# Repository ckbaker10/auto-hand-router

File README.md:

# Auto-Hand-Router

Curved tracks and teardrops for two-layer KiCad 10 boards.

Freerouting or J-Kreisel handles the connections. Auto-Hand-Router spreads and
smooths the tracks, adds teardrops and checks the result.

## Demos

### 555 timer

Eight nets, 291 native arcs and ten vias. Uses the built-in reference router.

[KiCad project](examples/555-reference/routed.kicad_pro) ·
[Board source and license](examples/555-reference/SOURCE-LICENSE.txt)

### Drying Oven Compact

70 × 90 mm, 2,287 arcs, 43 vias and 229 teardrop shoulders.
No ERC, DRC or schematic parity findings.

[KiCad project](examples/drying-oven-compact/drying-oven-compact.kicad_pro) ·
[Results](examples/drying-oven-compact/summary.json)

### Drying Fridge

120 × 100 mm, 2,568 arcs, 45 vias and 274 teardrop shoulders.
All connections closed. Existing library and metadata warnings are listed in the results.

[KiCad project](examples/drying-fridge/drying-fridge.kicad_pro) ·
[Results](examples/drying-fridge/summary.json)

### Pad and via transitions

Teardrops follow straight tracks and native arcs, including offset entries and
short connected pieces. Default size: 0.875.

## Setup

Linux, Python 3.12+, [uv](https://docs.astral.sh/uv/) and KiCad 10 with its
`pcbnew` Python module. Components must be on the front side.

```sh
git clone https://github.com/ckbaker10/auto-hand-router.git
cd auto-hand-router
uv sync --locked

kicad-cli version
/usr/bin/python3 -c 'import pcbnew; print(pcbnew.Version())'
```

If KiCad uses a different interpreter or is outside your PATH:

```sh
export AUTO_HAND_ROUTER_KICAD_CLI=/path/to/kicad-cli
export AUTO_HAND_ROUTER_KICAD_PYTHON=/path/to/python3
```

For the `route` command, choose one backend.

### Freerouting

Requires Java 25. Download the pinned 2.5.0 JAR:

```sh
mkdir -p "$HOME/.local/share/auto-hand-router"
curl -fL https://github.com/freerouting/freerouting/releases/download/v2.5.0/freerouting-2.5.0.jar \
  -o "$HOME/.local/share/auto-hand-router/freerouting-2.5.0.jar"

export AUTO_HAND_ROUTER_FREEROUTING_JAR="$HOME/.local/share/auto-hand-router/freerouting-2.5.0.jar"
```

The router checks the JAR checksum.

### J-Kreisel

```sh
uv sync --locked --extra kreisel
```

A Rust toolchain may be needed to build it. Use
`uv run --locked --extra kreisel auto-hand-router route --backend kreisel`
with the board, output and work options below.

## Route a board

Keep the PCB, project and schematic together with the same filename stem:
`controller.kicad_pcb`, `controller.kicad_pro`, `controller.kicad_sch`.
Existing project rules and library tables are used.

```sh
uv run --locked auto-hand-router route \
  --board /path/to/controller.kicad_pcb \
  --output-dir output/controller \
  --work-dir work/controller-001 \
  --spacing 1.2 \
  --teardrop-size 0.875
```

This uses Freerouting. The source project stays unchanged.
The output contains the KiCad project, SVG/PNG previews and `report.json`.
Use a new work directory for each run.

| Option | Effect |
| --- | --- |
| `--spacing 1.2` | Preferred extra clearance in mm. Minimum project clearances still apply. |
| `--via-policy courtyards` | Default. Keeps vias outside component courtyards. |
| `--via-policy module-interiors` | Allows vias under large through-hole modules. Pad, drill and keepout clearances still apply. |
| `--radius 2.5` | Maximum radius for local fallback fillets, in mm. |
| `--teardrop-size 0.875` | Scales teardrop length and shoulders. |
| `--no-teardrops` | Disables teardrops. |

Project netclasses are used by default. Add
`--profile profiles/jlcpcb-2layer-1oz.json` to apply the included profile.
For this profile, put your power nets in `kicad-workflow.json` next to the board:

```json
{"routing": {"power_net_patterns": ["/+5V", "/+3V3", "/GND"]}}
```

## Add teardrops to an existing board

```sh
uv run --locked auto-hand-router teardrops \
  --board /path/to/controller.kicad_pcb \
  --output-dir output/controller-teardrops \
  --work-dir work/controller-teardrops-001 \
  --size 0.875
```

This keeps the existing tracks and adds copper zones at pads and vias.
Both directories must be new. Use `--length-ratio` and `--max-length` to
adjust the shape. Add `--via-policy module-interiors` if the board already
uses vias under modules.

## Reproduce the demos

The routed projects shown above are included in `examples/`.

Generate the 555 routing and then add teardrops. No external routing backend is needed:

```sh
uv run --locked auto-hand-router --comparison --output-dir output/555

uv run --locked auto-hand-router teardrops \
  --board output/555/routed.kicad_pcb \
  --output-dir output/555-teardrops \
  --work-dir work/555-teardrops-001
```

Rebuild teardrops and previews for the two larger demos:

```sh
uv run --locked auto-hand-router teardrops \
  --board examples/drying-oven-compact/drying-oven-compact.kicad_pcb \
  --output-dir output/oven-teardrops \
  --work-dir work/oven-teardrops-001 \
  --via-policy module-interiors

uv run --locked auto-hand-router teardrops \
  --board examples/drying-fridge/drying-fridge.kicad_pcb \
  --output-dir output/fridge-teardrops \
  --work-dir work/fridge-teardrops-001
```

To reroute either project, use its PCB with the `route` command.
The Compact uses J-Kreisel; the Fridge uses Freerouting.

Run the checks and build the package:

```sh
uv run --locked pytest -q
uv run --locked ruff check auto_hand_router comparison tests tools/sync_project_examples.py
uv build
```

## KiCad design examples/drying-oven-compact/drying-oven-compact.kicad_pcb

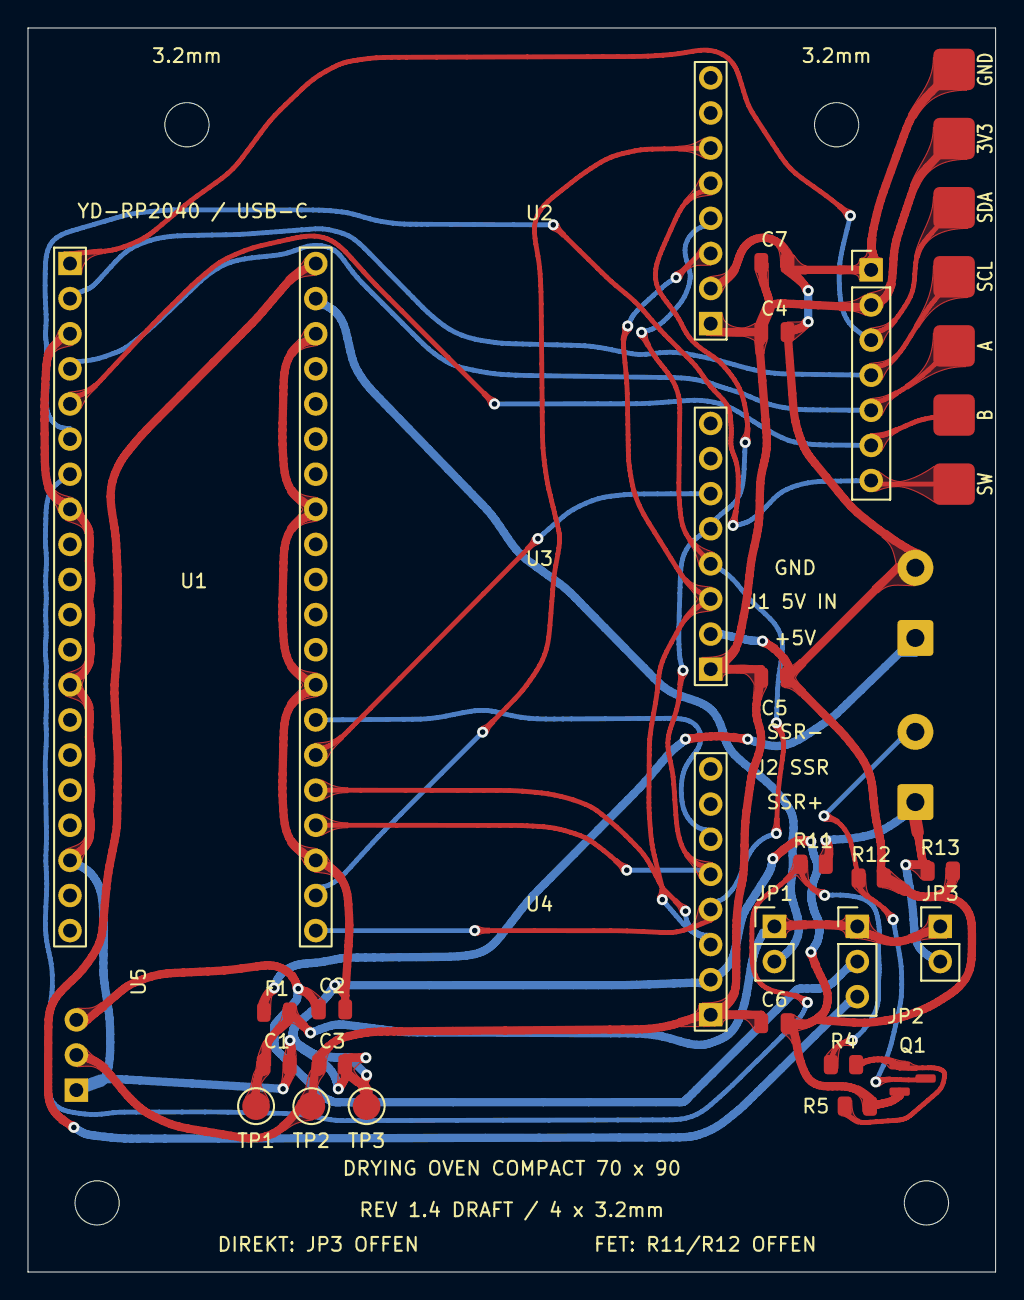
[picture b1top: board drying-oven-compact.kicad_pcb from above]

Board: 2 copper layers, 70.0 x 90.0 mm, 33 parts (0 on the bottom side), 22 nets.

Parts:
C1, C2, C3: 10u / 10V; JLC_C_0805_2012Metric
C4, C5, C6, C7: 100n / 10V; JLC_C_0805_2012Metric
F1: 0.5A HOLD / >=6V; JLC_Fuse_0805_2012Metric
H1, H2, H3, H4: M3; MountingHole_3.2mm_M3
J1: PS1 -> TRAEGER / 5V; TerminalBlock_1x02_P5.08_SilkClear
J2: SSR STEUERKABEL; TerminalBlock_1x02_P5.08_SilkClear
J3: DISPLAY-LOETPADS; Display_Wire_SolderPads_1x07
J4: STECKEROPTION VORDERSEITE / DNP; JLC_PinHeader_1x07_P2.54mm_Vertical
JP1: MCU VIN FREIGABE; JLC_PinHeader_1x02_P2.54mm_Vertical
JP2: REG: 1-2 PSU / 2-3 USB; JLC_PinHeader_1x03_P2.54mm_Vertical
JP3: 5V NUR FET / OFFEN BEI DIREKT; JLC_PinHeader_1x02_P2.54mm_Vertical
Q1: AO3400A; JLC_SOT-23
R4: 100R; JLC_R_0805_2012Metric
R5: 100k / AUS BEI RESET; JLC_R_0805_2012Metric
R11, R12: 0R / NUR DIREKT; JLC_R_0805_2012Metric
R13: 10k / OPTIONAL DNP; JLC_R_0805_2012Metric
TP1: +5V_MAIN; JLC_TestPoint_Pad_D2.0mm
TP2: +3V3_EXT; JLC_TestPoint_Pad_D2.0mm
TP3: GND; JLC_TestPoint_Pad_D2.0mm
U1: RP2040 USB-C / 16MiB; JLC_YD_RP2040_40Pin_Socket
U2: MAX31856 / T1; JLC_MAX31856_D25_W23_8Pin_Socket_DRAFT
U3: MAX31856 / T2; JLC_MAX31856_D25_W23_8Pin_Socket_DRAFT
U4: MAX31856 / T3; JLC_MAX31856_D25_W23_8Pin_Socket_DRAFT
U5: AMS1117 Modul / 3.3V; AMS1117_Module_3Pin_DRAFT

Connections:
/+3V3_EXT: C3.1, C4.1, C5.1, C6.1, C7.1, J3.2, J4.2, TP2.1, U2.1, U3.1, U4.1, U5.2
/+5V_MAIN: C1.1, F1.2, JP1.1, JP2.1, JP3.1, TP1.1
/ENC_A: J3.5, J4.5, U1.4
/ENC_B: J3.6, J4.6, U1.5
/ENC_SW: J3.7, J4.7, U1.6
/GND: C1.2, C2.2, C3.2, C4.2, C5.2, C6.2, C7.2, J1.2, J3.1, J4.1, Q1.2, R5.2, R12.2, R13.2, TP3.1, U1.3, U1.8, U1.13, U1.18, U1.23, U1.28, U1.33, U1.38, U2.2, U3.2, U4.2, U5.1
/I2C_SCL: J3.4, J4.4, U1.2
/I2C_SDA: J3.3, J4.3, U1.1
/MCU_VIN: JP1.2, U1.39
/MCU_VOUT: JP2.3, U1.40
/PSU_5V_RAW: F1.1, J1.1
/REG_5V_IN: C2.1, JP2.2, U5.3
/SPI_MISO: U1.21, U2.4, U3.4, U4.4
/SPI_MOSI: U1.25, U2.3, U3.3, U4.3
/SPI_SCK: U1.24, U2.5, U3.5, U4.5
/SSR_CMD: R4.1, R11.1, U1.7
/SSR_GATE: Q1.1, R4.2, R5.1
/SSR_NEG: J2.2, Q1.3, R12.1
/SSR_POS: J2.1, JP3.2, R11.2, R13.1
/TC_CS1: U1.22, U2.6
/TC_CS2: U1.26, U3.6
/TC_CS3: U1.27, U4.6

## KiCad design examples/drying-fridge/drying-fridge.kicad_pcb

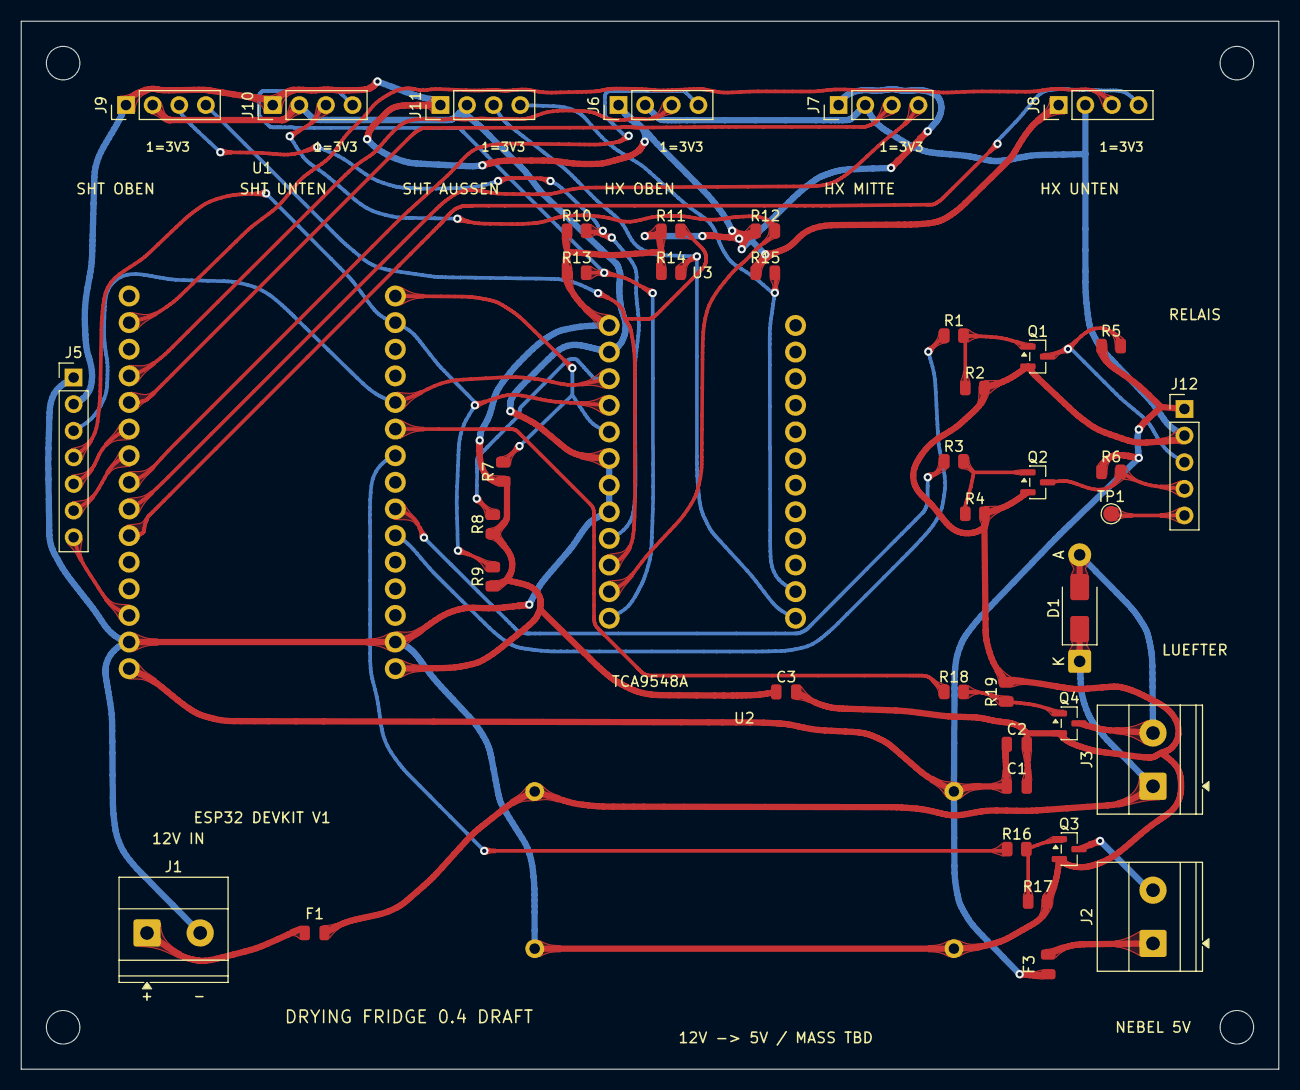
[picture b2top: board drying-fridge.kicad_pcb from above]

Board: 2 copper layers, 120.0 x 100.0 mm, 58 parts (0 on the bottom side), 37 nets.

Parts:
C1: 10u / >=10V; JLC_C_0805_2012Metric
C2, C3: 100n; JLC_C_0805_2012Metric
CT1: Kabelbinder J6; CableTie_2Slots_3.5x1.5_S8_DRAFT
CT2: Kabelbinder J7; CableTie_2Slots_3.5x1.5_S8_DRAFT
CT3: Kabelbinder J8; CableTie_2Slots_3.5x1.5_S8_DRAFT
CT4: Kabelbinder J9; CableTie_2Slots_3.5x1.5_S8_DRAFT
CT5: Kabelbinder J10; CableTie_2Slots_3.5x1.5_S8_DRAFT
CT6: Kabelbinder J11; CableTie_2Slots_3.5x1.5_S8_DRAFT
CT7: Kabelbinder J1; CableTie_2Slots_3.5x1.5_S8_DRAFT
CT8: Kabelbinder J2; CableTie_2Slots_3.5x1.5_S8_DRAFT
CT9: Kabelbinder J3; CableTie_2Slots_3.5x1.5_S8_DRAFT
CT10: Kabelbinder J12; CableTie_2Slots_3.5x1.5_S8_DRAFT
D1: Freilauf / Typ TBD; D_SMA_DO41_Combo_P10.16mm_D1.1
F1: AUX / Wert TBD; JLC_Fuse_0805_2012Metric
F3: NEBEL / Wert TBD; JLC_Fuse_0805_2012Metric
H1, H2, H3, H4: MountingHole_3.2mm_M3
J1: 12V IN / Versorgung; TerminalBlock_Phoenix_MKDS-1,5-2-5.08_1x02_P5.08mm_Horizont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
J2: NEBEL + / RETURN; TerminalBlock_Phoenix_MKDS-1,5-2-5.08_1x02_P5.08mm_Horizont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
J3: FAN power connector; TerminalBlock_Phoenix_MKDS-1,5-2-5.08_1x02_P5.08mm_Horizont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
J5: OLED / EC11 / 3V3 / OPTION; PinHeader_1x07_P2.54mm_Vertical
J6: HX711 OBEN; PinHeader_1x04_P2.54mm_Vertical
J7: HX711 MITTE; PinHeader_1x04_P2.54mm_Vertical
J8: HX711 UNTEN; PinHeader_1x04_P2.54mm_Vertical
J9: SHT40 OBEN; PinHeader_1x04_P2.54mm_Vertical
J10: SHT40 UNTEN; PinHeader_1x04_P2.54mm_Vertical
J11: SHT40 AUSSEN; PinHeader_1x04_P2.54mm_Vertical
J12: RELAIS STEUERUNG; PinHeader_1x05_P2.54mm_Vertical
Q1, Q2, Q3, Q4: AO3400A; SOT-23
R1, R3, R16, R18: 100; JLC_R_0805_2012Metric
R2, R4, R17, R19: 100k; JLC_R_0805_2012Metric
R5, R6, R7: 10k; JLC_R_0805_2012Metric
R8, R9, R10, R11, R12, R13, R14, R15: 4k7 DNP; JLC_R_0805_2012Metric
TP1: CTRL_COM / Modul pruefen; TestPoint_Pad_D1.5mm
U1: ESP32 DEVKIT V1 / ESP-WROOM-32 / 30pin; ESP32_DevKitV1_30Pin_D1.2_REF_DRAFT
U2: DC/DC 12V -> 5V / TBD; Fridge_DCDC_4Terminal_EST_DRAFT
U3: TCA9548A HW-617; TCA9548A_HW617_22x31_P17.78_D1.2_DRAFT

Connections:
/+3V3: C3.1, J5.2, J6.1, J7.1, J8.1, J9.1, J10.1, J11.1, R7.1, R8.1, R9.1, R10.1, R11.1, R12.1, R13.1, R14.1, R15.1, U1.R15 (3V3), U3.VIN
/+5V: C1.1, C2.1, F3.1, J12.1, R5.1, R6.1, U1.L15 (VIN), U2.OUT+
/+5V_MIST: F3.2, J2.1
/+12V_AUX: D1.1, F1.2, J3.1, U2.IN+
/+12V_IN: F1.1, J1.1
/ENC_A: J5.5, U1.L6 (D32_GPIO32)
/ENC_B: J5.6, U1.L7 (D33_GPIO33)
/ENC_SW: J5.7, U1.L13 (D13_GPIO13)
/FAN_EN: R18.1, U1.R6 (D19_GPIO19)
/FAN_GATE: Q4.1, R18.2, R19.1
/FAN_RETURN: D1.2, J3.2, Q4.3
/FRIDGE_EN: R3.1, U1.R9 (TX2_GPIO17)
/GND: C1.2, C2.2, C3.2, J1.2, J5.1, J6.2, J7.2, J8.2, J9.2, J10.2, J11.2, J12.2, Q1.2, Q2.2, Q3.2, Q4.2, R2.2, R4.2, R17.2, R19.2, U1.L14 (GND), U1.R14 (GND), U2.IN-, U2.OUT-, U3.A0, U3.A1, U3.A2, U3.GND
/HEAT_EN: R1.1, U1.R10 (RX2_GPIO16)
/HX_LOW_DT: J8.3, U1.L2 (VP_GPIO36)
/HX_LOW_SCK: J8.4, U1.L10 (D27_GPIO27)
/HX_MID_DT: J7.3, U1.L5 (D35_GPIO35)
/HX_MID_SCK: J7.4, U1.L9 (D26_GPIO26)
/HX_TOP_DT: J6.3, U1.L4 (D34_GPIO34)
/HX_TOP_SCK: J6.4, U1.L8 (D25_GPIO25)
/I2C_MUX_RST: R7.2, U1.R1 (D23_GPIO23), U3.RST
/I2C_SCL: J5.4, R9.2, U1.R2 (D22_GPIO22), U3.SCL
/I2C_SDA: J5.3, R8.2, U1.R5 (D21_GPIO21), U3.SDA
/MIST_EN: R16.1, U1.R7 (D18_GPIO18)
/MIST_GATE: Q3.1, R16.2, R17.1
/MIST_RETURN: J2.2, Q3.3
/RELAY_CTRL_COM: J12.5, TP1.1
/RELAY_GATE_1: Q1.1, R1.2, R2.1
/RELAY_GATE_2: Q2.1, R3.2, R4.1
/RELAY_IN1: J12.3, Q1.3, R5.2
/RELAY_IN2: J12.4, Q2.3, R6.2
/SHT_LOW_SCL: J10.4, R13.2, U3.SC1
/SHT_LOW_SDA: J10.3, R12.2, U3.SD1
/SHT_OUT_SCL: J11.4, R15.2, U3.SC2
/SHT_OUT_SDA: J11.3, R14.2, U3.SD2
/SHT_TOP_SCL: J9.4, R11.2, U3.SC0
/SHT_TOP_SDA: J9.3, R10.2, U3.SD0

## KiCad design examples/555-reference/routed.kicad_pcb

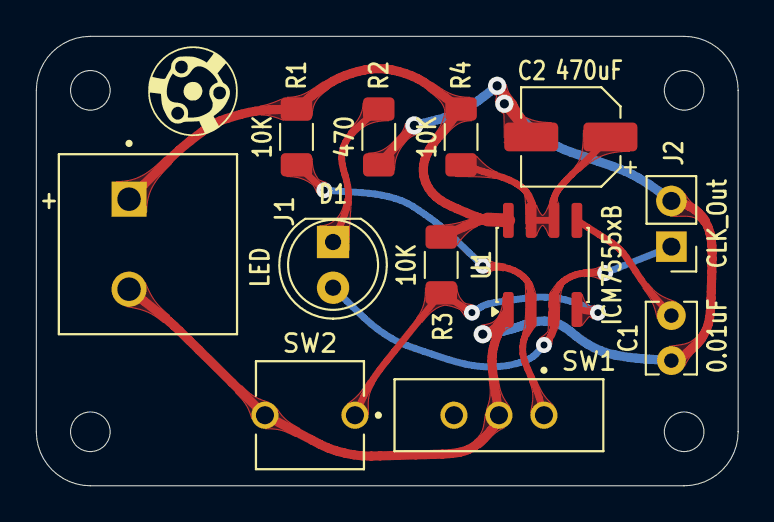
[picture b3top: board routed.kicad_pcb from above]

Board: 2 copper layers, 39.0 x 25.0 mm, 16 parts (0 on the bottom side), 8 nets.

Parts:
C1: 0.01uF; C_Disc_D3.8mm_W2.6mm_P2.50mm
C2: 470uF; CP_Elec_5x5.4
D1: LED; LED_D5.0mm
H1, H2, H3, H4: MountingHole; MountingHole_2.2mm_M2
J1: +5V; Terminal_Block_5mm
J2: CLK_Out; PinHeader_1x02_P2.54mm_Vertical
R1, R3, R4: 10K; R_1206_3216Metric_Pad1.30x1.75mm_HandSolder
R2: 470; R_1206_3216Metric_Pad1.30x1.75mm_HandSolder
SW1: Trigger; slide_switch_2.54mm
SW2: RST; tact_switch_5mm
U1: ICM7555xB; SOIC-8_3.9x4.9mm_P1.27mm

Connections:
/+5V: J1.1, R1.2, R3.2, R4.2, U1.8 (VCC)
/CLK_Out: D1.2 (A), J2.1, U1.3 (OUT)
/RST: R3.1, SW2.1, U1.4 (~RST)
/Trigger: R1.1, SW1.1 (A), U1.2 (TRIG)
GND: C1.2, C2.2, J1.2, J2.2, R2.1, SW1.2 (B), SW2.2, U1.1 (GND)
unnamed: D1.1 (K), R2.2
unnamed: C1.1, U1.5 (CONT)
unnamed: C2.1, R4.1, U1.6 (THRES), U1.7 (DISCH)

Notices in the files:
parts and their libraries:
Derived from KiCad TerminalBlock_Phoenix MKDS-1,5-2-5.08, CC-BY-SA-4.0 with KiCad exception. Same pads/body/courtyard/3D. Silkscreen shapes omitted to avoid clipping in this carrier placement.
